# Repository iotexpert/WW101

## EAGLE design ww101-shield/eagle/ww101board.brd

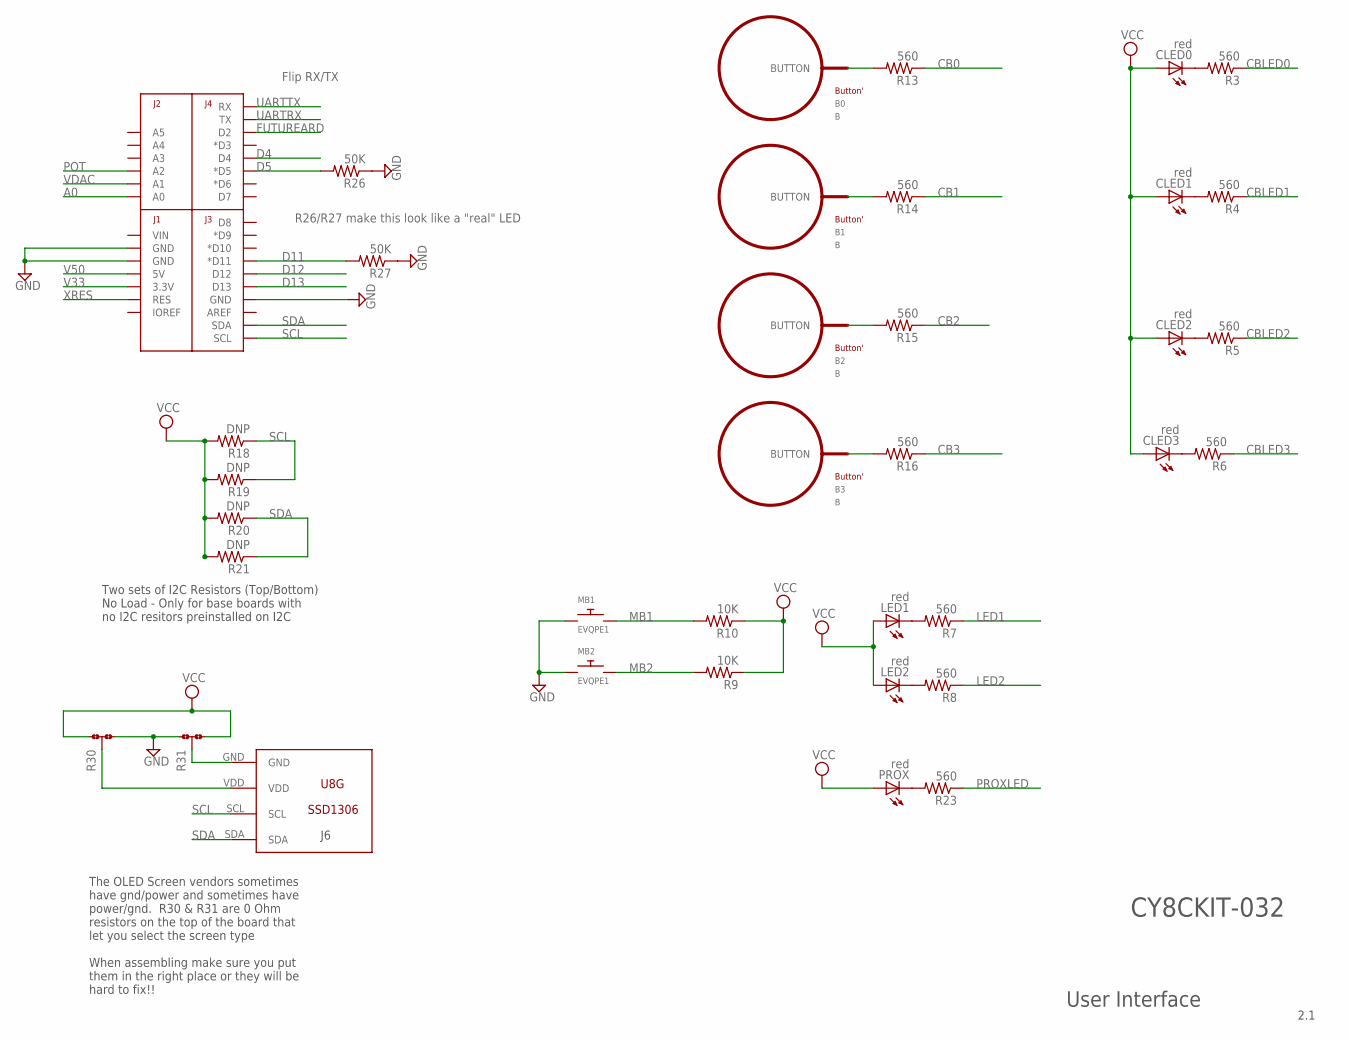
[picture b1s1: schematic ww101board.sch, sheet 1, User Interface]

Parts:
B0, B1, B2, B3: B; BUTTON_PASSIVE_10MM
CLED0, CLED1, CLED2, CLED3: red; CHIP-LED0603
J6: U8G-096-OLED; 096-SSD1306
LED1, LED2: red; CHIP-LED0603
MB1, MB2: EVQPE1; SWITCH
PROX: red; CHIP-LED0603
R3, R4, R5, R6, R7, R8, R13, R14, R15, R16, R23: 560; 0603-RES
R9, R10: 10K; 0603-RES
R18, R19, R20, R21: DNP; 0603-RES
R26, R27: 50K; 0603-RES
R30: JMP-3-1_2
R31: JMP-3-2_3
U$1: ARDUINO_R3_SHIELDNOLABELS; UNO_R3_SHIELD_NOLABELS

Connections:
A0: U$1.A0; also elsewhere on the board
CB0: R13.1; also elsewhere on the board
CB1: R14.1; also elsewhere on the board
CB2: R15.1; also elsewhere on the board
CB3: R16.1; also elsewhere on the board
CBLED0: R3.1; also elsewhere on the board
CBLED1: R4.1; also elsewhere on the board
CBLED2: R5.1; also elsewhere on the board
CBLED3: R6.1; also elsewhere on the board
D4: U$1.D4; also elsewhere on the board
D5: R26.2, U$1.D5 (*D5); also elsewhere on the board
D11: R27.2, U$1.D11 (*D11); also elsewhere on the board
D12: U$1.D12; also elsewhere on the board
D13: U$1.D13; also elsewhere on the board
FUTUREARD: U$1.D2; also elsewhere on the board
GND: MB1.P$1, MB2.P$1, R26.1, R27.1, R30.3, R31.1, U$1.GND@0 (GND), U$1.GND@1 (GND), U$1.GND@2 (GND); also elsewhere on the board
LED1: R7.1; also elsewhere on the board
LED2: R8.1; also elsewhere on the board
MB1: MB1.P$2, R10.2; also elsewhere on the board
MB2: MB2.P$2, R9.2; also elsewhere on the board
unnamed: B0.BUTTON, R13.2
unnamed: PROX.C, R23.2
unnamed: B1.BUTTON, R14.2
unnamed: B2.BUTTON, R15.2
unnamed: CLED0.C, R3.2
unnamed: CLED1.C, R4.2
unnamed: CLED2.C, R5.2
unnamed: CLED3.C, R6.2
unnamed: LED1.C, R7.2
unnamed: LED2.C, R8.2
unnamed: J6.VDD, R30.2
unnamed: B3.BUTTON, R16.2
unnamed: J6.GND, R31.2
POT: U$1.A2; also elsewhere on the board
PROXLED: R23.1; also elsewhere on the board
SCL: J6.SCL, R18.1, R19.1, U$1.SCL; also elsewhere on the board
SDA: J6.SDA, R20.1, R21.1, U$1.SDA; also elsewhere on the board
UARTRX: U$1.TX; also elsewhere on the board
UARTTX: U$1.RX; also elsewhere on the board
V33: U$1.3.3V; also elsewhere on the board
V50: U$1.5V; also elsewhere on the board
VCC: CLED0.A, CLED1.A, CLED2.A, CLED3.A, LED1.A, LED2.A, PROX.A, R9.1, R10.1, R18.2, R19.2, R20.2, R21.2, R30.1, R31.3; also elsewhere on the board
VDAC: U$1.A1; also elsewhere on the board
XRES: U$1.RES; also elsewhere on the board

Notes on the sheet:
Flip RX/TX
User Interface
Two sets of I2C Resistors (Top/Bottom) No Load - Only for base boards with no I2C resitors preinstalled on I2C
The OLED Screen vendors sometimes have gnd/power and sometimes have power/gnd. R30 & R31 are 0 Ohm resistors on the top of the board that let you select the screen type When assembling make sure you put them in the right place or they will be hard to fix!!
2.1
CY8CKIT-032
R26/R27 make this look like a "real" LED

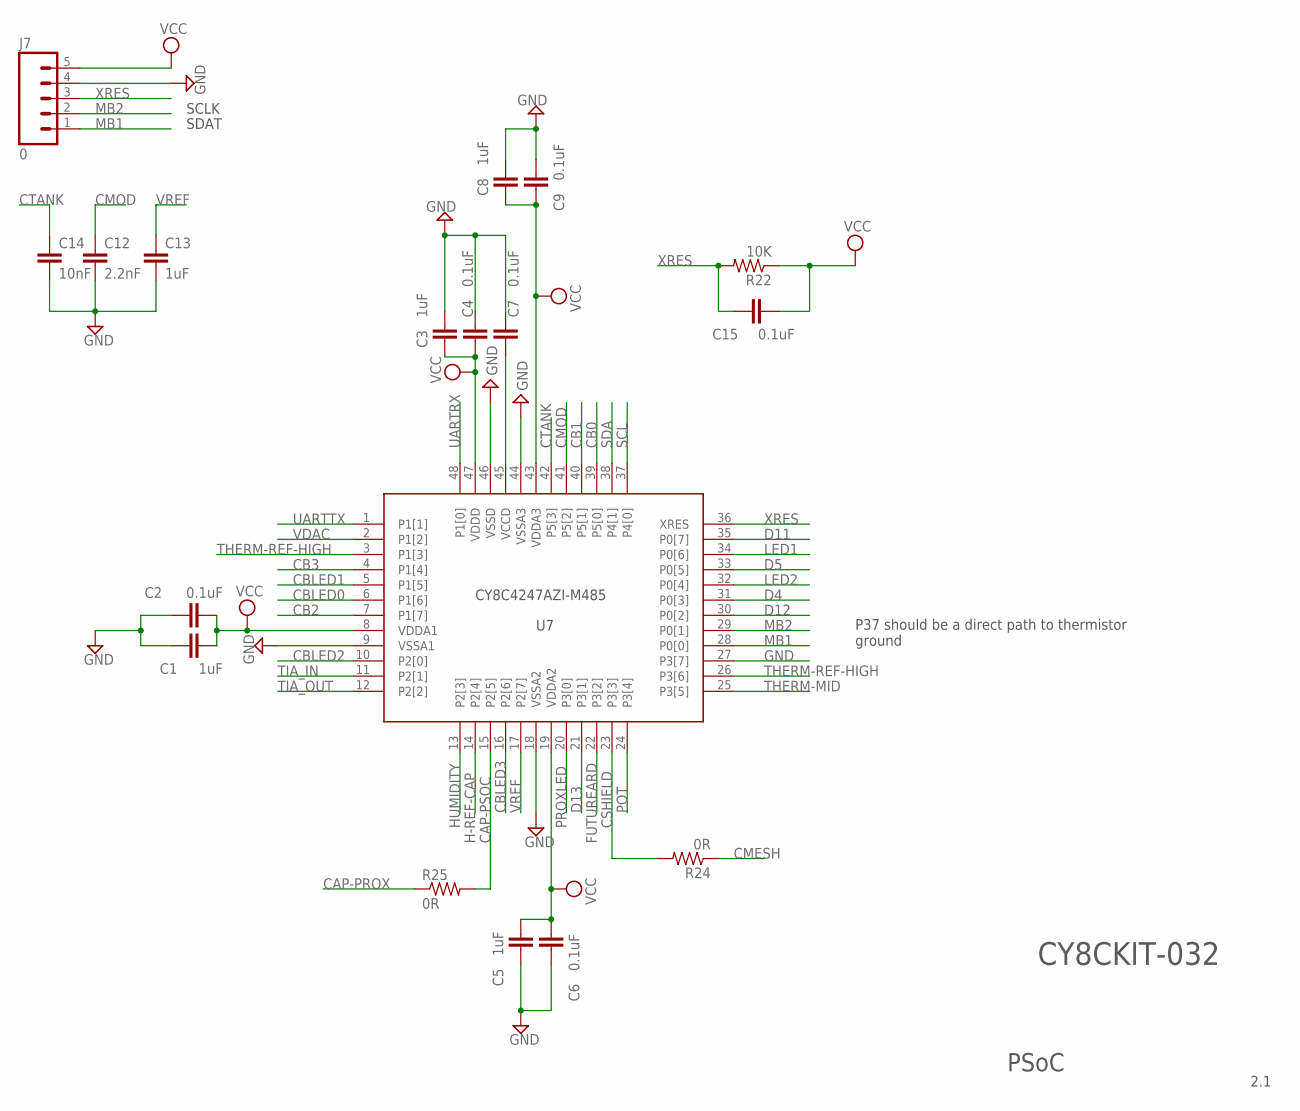
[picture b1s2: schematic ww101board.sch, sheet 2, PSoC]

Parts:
C1, C3, C5, C8, C13: 1uF; 0603-CAP
C2, C4, C6, C7, C9, C15: 0.1uF; 0603-CAP
C12: 2.2nF; 0603-CAP
C14: 10nF; 0603-CAP
J7: 0; 1X05_LOCK
R22: 10K; 0603-RES
R24, R25: 0R; 0603-RES
U7: CY8C4A45-48; TQFP-7X7-48
U$7: CYLOGO-SILK

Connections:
CAP-PROX: R25.1
CAP-PSOC: R25.2, U7.15 (P2[5])
CB0: U7.39 (P5[0]); also elsewhere on the board
CB1: U7.40 (P5[1]); also elsewhere on the board
CB2: U7.7 (P1[7]); also elsewhere on the board
CB3: U7.4 (P1[4]); also elsewhere on the board
CBLED0: U7.6 (P1[6]); also elsewhere on the board
CBLED1: U7.5 (P1[5]); also elsewhere on the board
CBLED2: U7.10 (P2[0]); also elsewhere on the board
CBLED3: U7.16 (P2[6]); also elsewhere on the board
CMESH: R24.1
CMOD: C12.1, U7.41 (P5[2])
CSHIELD: R24.2, U7.23 (P3[3])
CTANK: C14.1, U7.42 (P5[3])
D4: U7.31 (P0[3]); also elsewhere on the board
D5: U7.33 (P0[5]); also elsewhere on the board
D11: U7.35 (P0[7]); also elsewhere on the board
D12: U7.30 (P0[2]); also elsewhere on the board
D13: U7.21 (P3[1]); also elsewhere on the board
FUTUREARD: U7.22 (P3[2]); also elsewhere on the board
GND: C1.1, C2.1, C3.1, C4.1, C5.2, C6.2, C7.1, C8.1, C9.1, C12.2, C13.2, C14.2, J7.4, U7.9 (VSSA1), U7.18 (VSSA2), U7.27 (P3[7]), U7.44 (VSSA3), U7.46 (VSSD); also elsewhere on the board
H-REF-CAP: U7.14 (P2[4]); also elsewhere on the board
HUMIDITY: U7.13 (P2[3]); also elsewhere on the board
LED1: U7.34 (P0[6]); also elsewhere on the board
LED2: U7.32 (P0[4]); also elsewhere on the board
MB1: J7.1, U7.28 (P0[0]); also elsewhere on the board
MB2: J7.2, U7.29 (P0[1]); also elsewhere on the board
unnamed: C7.2, U7.45 (VCCD)
POT: U7.24 (P3[4]); also elsewhere on the board
PROXLED: U7.20 (P3[0]); also elsewhere on the board
SCL: U7.37 (P4[0]); also elsewhere on the board
SDA: U7.38 (P4[1]); also elsewhere on the board
THERM-MID: U7.25 (P3[5]); also elsewhere on the board
THERM-REF-HIGH: U7.3 (P1[3]), U7.26 (P3[6]); also elsewhere on the board
TIA_IN: U7.11 (P2[1]); also elsewhere on the board
TIA_OUT: U7.12 (P2[2]); also elsewhere on the board
UARTRX: U7.48 (P1[0]); also elsewhere on the board
UARTTX: U7.1 (P1[1]); also elsewhere on the board
VCC: C1.2, C2.2, C3.2, C4.2, C5.1, C6.1, C8.2, C9.2, C15.1, J7.5, R22.1, U7.8 (VDDA1), U7.19 (VDDA2), U7.43 (VDDA3), U7.47 (VDDD); also elsewhere on the board
VDAC: U7.2 (P1[2]); also elsewhere on the board
VREF: C13.1, U7.17 (P2[7])
XRES: C15.2, J7.3, R22.2, U7.36 (XRES); also elsewhere on the board

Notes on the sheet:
SCLK
SDAT
PSoC
2.1
CY8C4247AZI-M485
CY8CKIT-032
P37 should be a direct path to thermistor ground

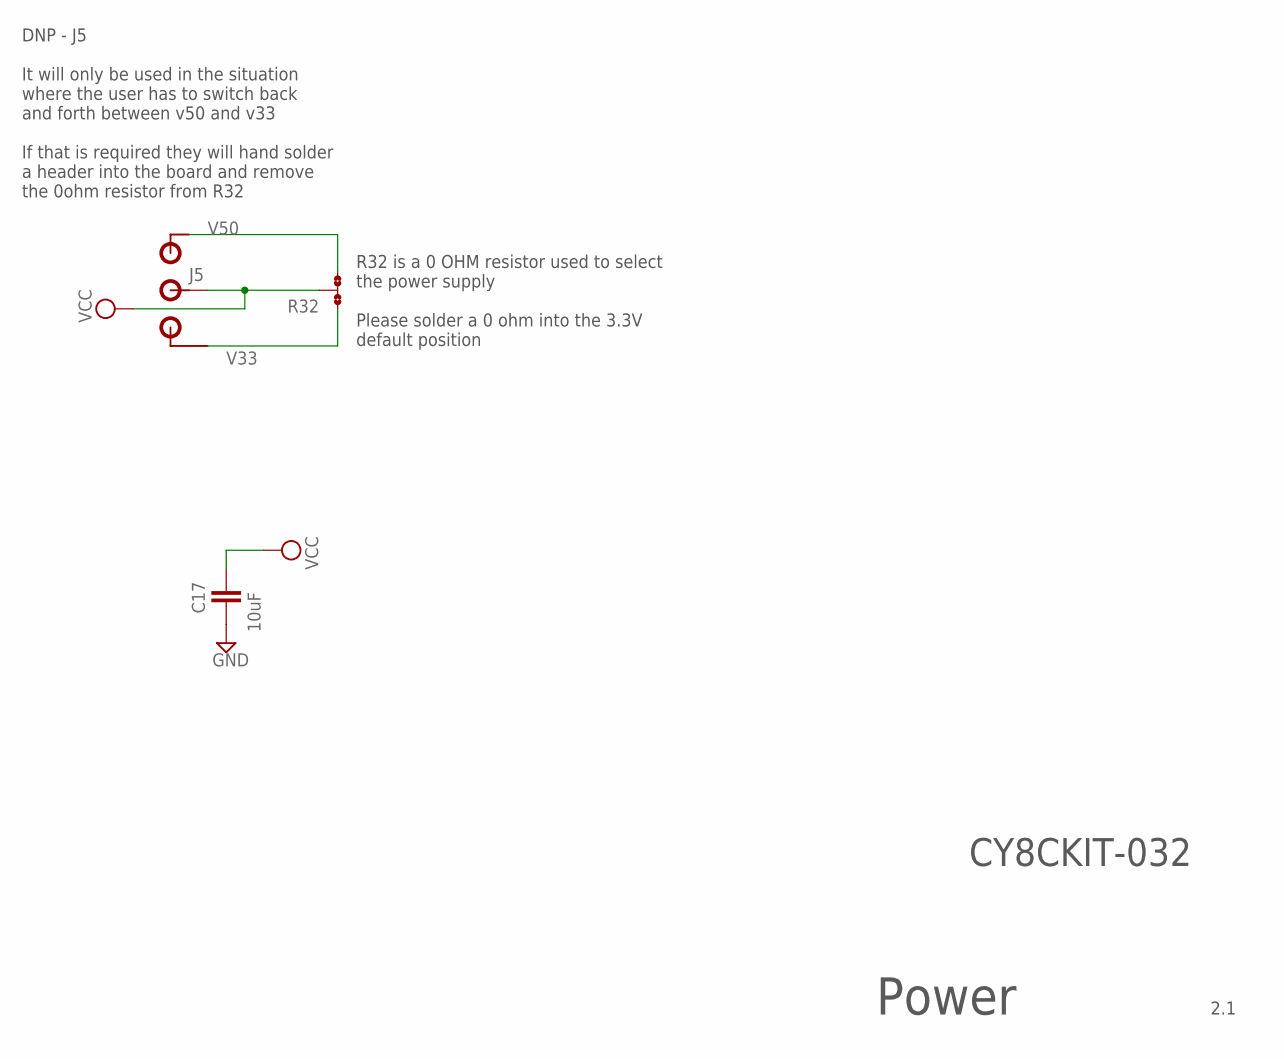
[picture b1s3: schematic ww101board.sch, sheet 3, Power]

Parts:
C17: 10uF; 0603-CAP
J5: JMP-3-PTH-PTH; JMP-3-NO-PTH-2.54
R32: JMP-3-NO

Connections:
GND: C17.2; also elsewhere on the board
V33: J5.3, R32.1; also elsewhere on the board
V50: J5.1, R32.3; also elsewhere on the board
VCC: C17.1, J5.2, R32.2; also elsewhere on the board

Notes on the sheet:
Power
2.1
DNP - J5 It will only be used in the situation where the user has to switch back and forth between v50 and v33 If that is required they will hand solder a header into the board and remove the 0ohm resistor from R32
R32 is a 0 OHM resistor used to select the power supply Please solder a 0 ohm into the 3.3V default position
CY8CKIT-032

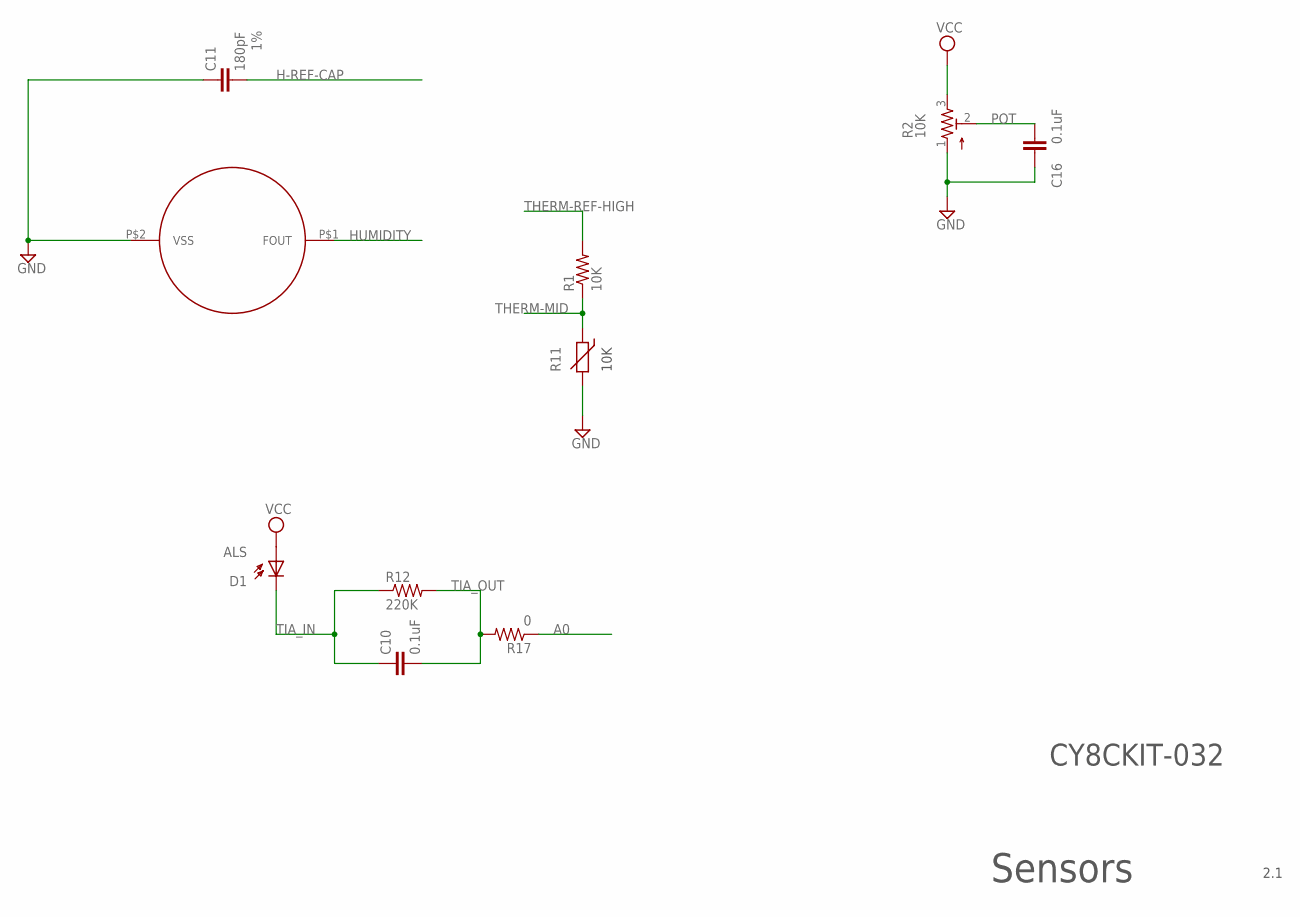
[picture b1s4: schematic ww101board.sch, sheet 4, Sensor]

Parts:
C10, C16: 0.1uF; 0603-CAP
C11: 180pF; 0603-CAP
D1: ALS
HUMIDITY: HPP801A031; HUMIDITY
R1: 10K; 0603-RES
R2: 10K; 3386P
R11: THERMISTOR-5; R-5
R12: 220K; 0603-RES
R17: 0; 0603-RES

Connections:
A0: R17.1; also elsewhere on the board
GND: C11.1, C16.2, HUMIDITY.P$2 (VSS), R2.1, R11.2; also elsewhere on the board
H-REF-CAP: C11.2; also elsewhere on the board
HUMIDITY: HUMIDITY.P$1 (FOUT); also elsewhere on the board
POT: C16.1, R2.2; also elsewhere on the board
THERM-MID: R1.1, R11.1; also elsewhere on the board
THERM-REF-HIGH: R1.2; also elsewhere on the board
TIA_IN: C10.1, D1.CATHODE (C1), R12.1; also elsewhere on the board
TIA_OUT: C10.2, R12.2, R17.2; also elsewhere on the board
VCC: D1.ANNODE (E1), R2.3; also elsewhere on the board

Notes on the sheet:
Sensors
10K
2.1
CY8CKIT-032

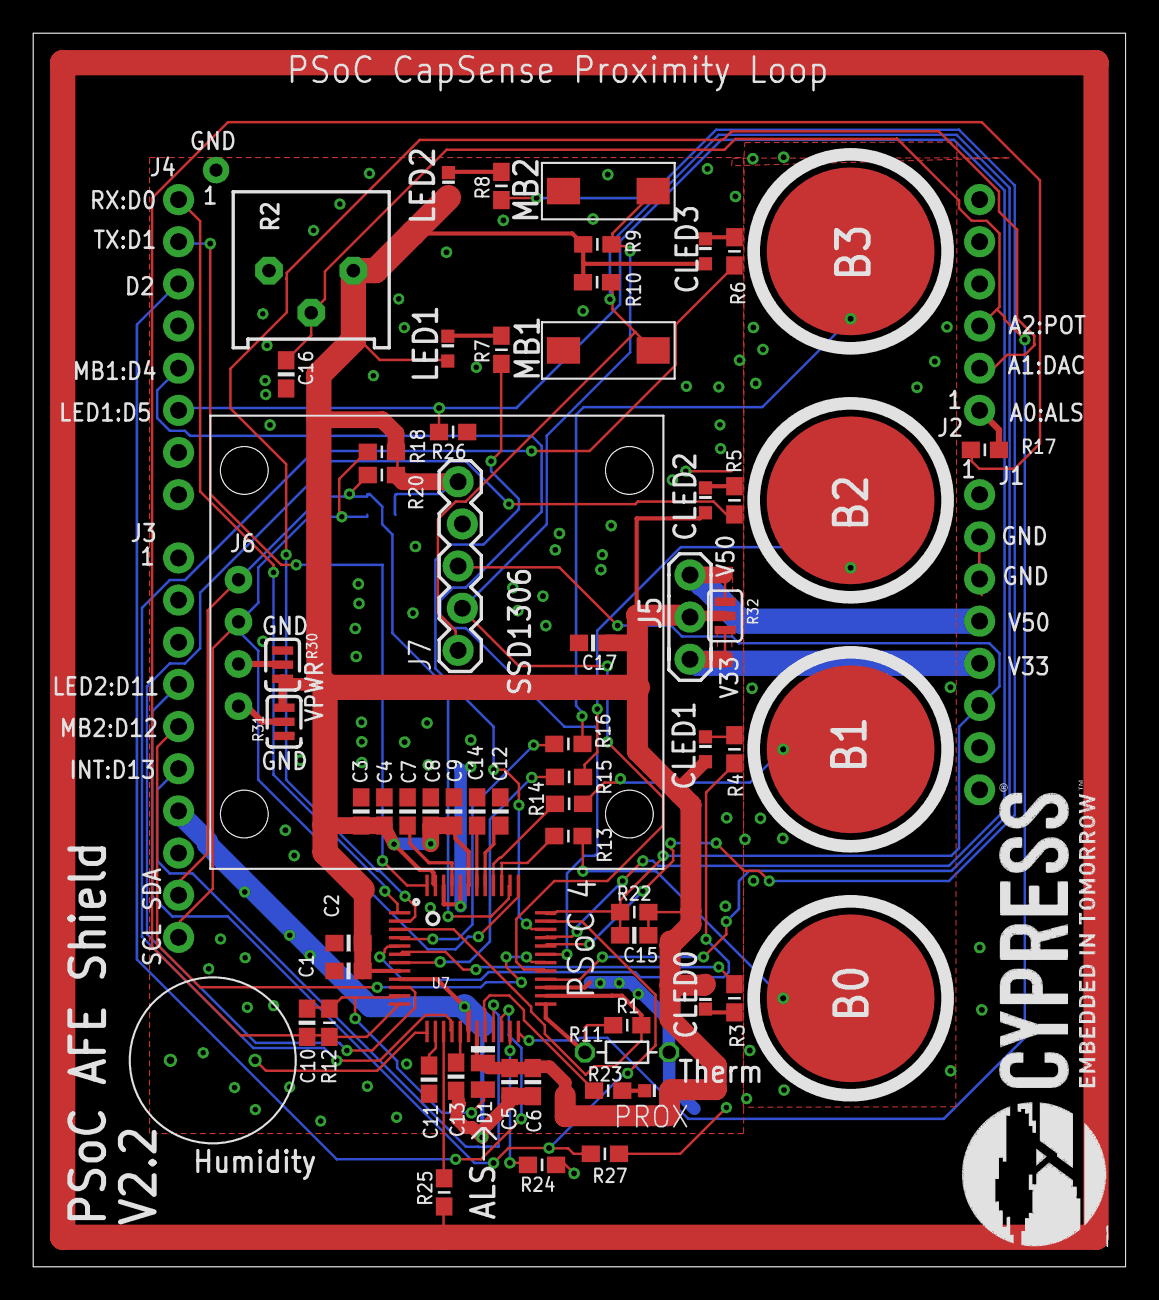
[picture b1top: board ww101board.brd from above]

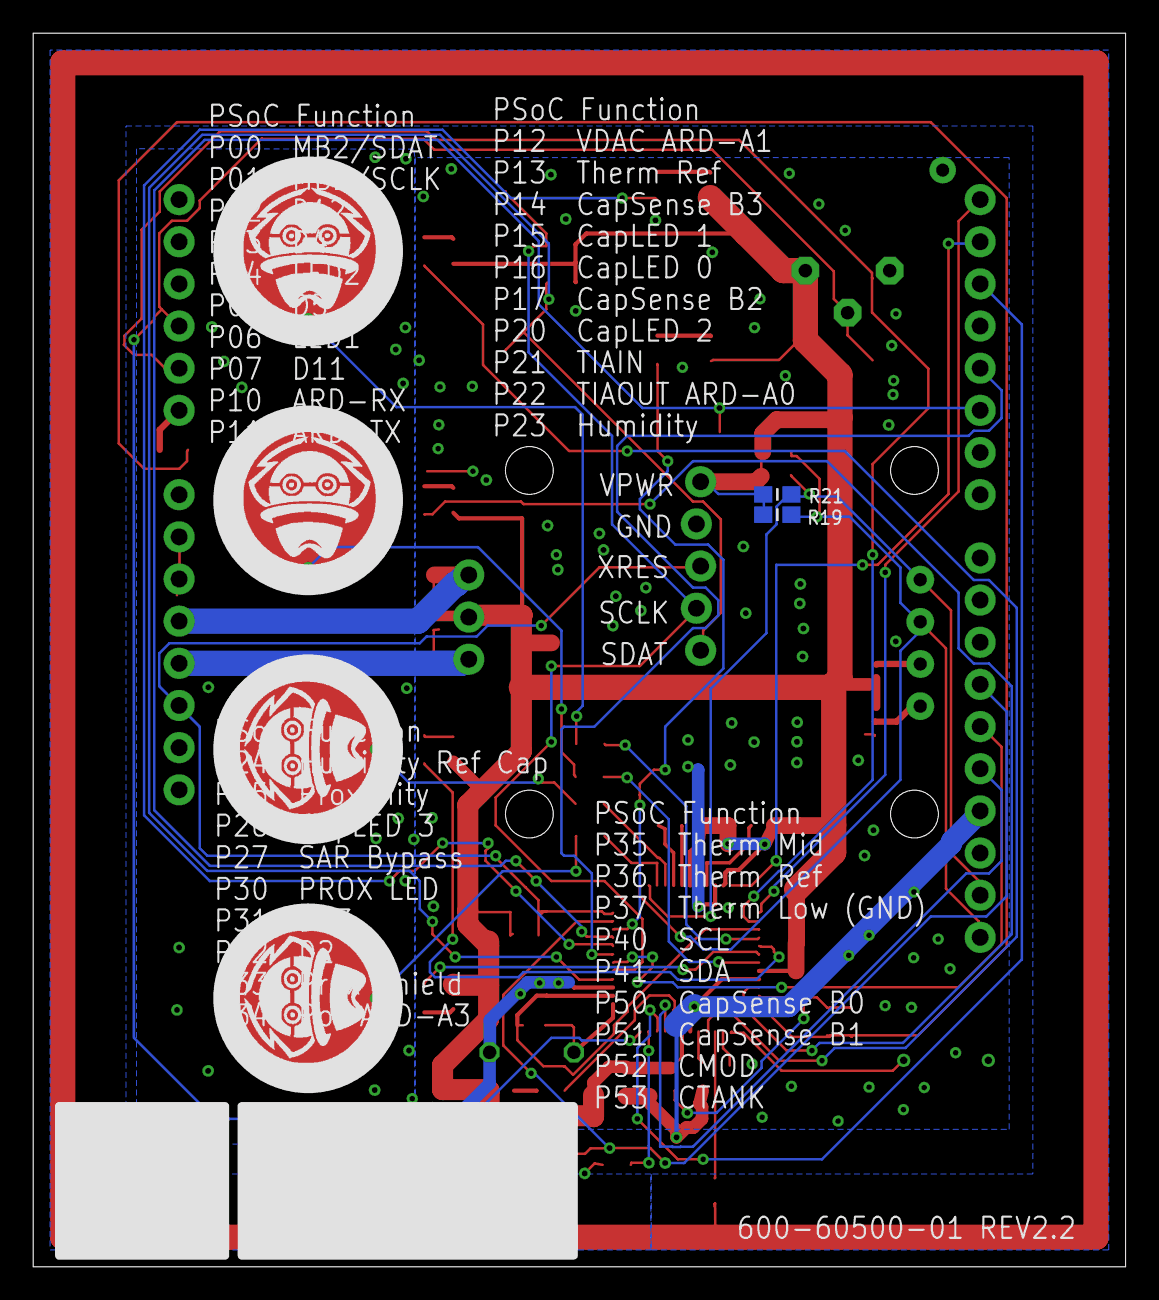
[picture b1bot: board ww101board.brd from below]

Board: 2 copper layers, 65.8 x 74.3 mm, 68 parts (2 on the bottom side), 56 nets.

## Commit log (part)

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2016-10-11 moved old single page lab manual
2016-10-12 Add material and exercises up through 10.
2016-10-12 Fix reference about USB connector on analog shield board.
2016-10-12 Move the WICED projects down one level.
2016-10-13 Bunches of updates to chapter 3,6,9
2016-10-13 Add BCM9493W Platform Files
2016-10-13 Add page numbers. Fix typos/wording. Fix figure for MUTEX documentation to be consistent with others.
2016-10-13 Add page numbers and make minor corrections.
2016-10-14 Remove .Greg file.
2016-10-15 Add codegentemp and .Greg to .gitignore. Update chapter 8. Fix PSoC project to have open drain, drives low on LED pins and to add external components to LEDs.
2016-10-17 Minor updates and type corrections.
2016-10-17 Checkin of labs for chapter 3 (RTOS).
2016-10-19 a little bit of reorganization
2016-10-19 project-list.xlsx
2016-10-19 Add example projects and errata sections. Fix typo in mutex project.
2016-10-20 first real draft of chapter 5
2016-10-20 updated based on JAMD comments
2016-10-21 Correct typos in chapters 00, 01, and 05
2016-10-21 a few updates to chapter 6'
2016-10-21 A bunch of updates
2016-10-22 Updates chapter 6a based on GJL and JAMD feedback
2016-10-22 massive updates to 5,6,7
2016-10-25 Formatting updates
2016-10-25 updated chapter 4
2016-10-25 Fix typos
2016-10-26 New answer key file and updates to 7a/7b.
2016-10-26 coverpage
2016-10-26 Initial checkin of chap 7b projects
2016-10-30 Updates after pilot class. Add pull down to LED pin on shield board
2016-10-31 Typo correction
2016-11-03 corrections in chapter 6 & make app name strings unique in project make files. git push origin gjl_oct23
    git status
2016-11-20 Updated the project and section for DCT in chapter 5
2016-11-20 Updates chapter 5 projects
2016-11-30 Updates to the server
2016-11-30 More updates to the TCP section
2016-12-02 fixed bug
2016-12-05 Updates prior to WW50 class. All projects and manuals modified for Wiced Studio 4.0 and other changes from pilot class.
2016-12-05 Rename labmanual files from WA101 to WW101 (WICED WiFi 101).
2016-12-05 Change project name from WA101 to WW101_AnalogCoprocessor
2017-01-24 smalls edits in chapters 2, 3, 5, 6. Full cleanup for chapters 0, 1
2017-01-31 Change TCP socket exampls to be stream first and packet second.
2017-01-31 add latest 048 files
2017-02-01 added a version number textbox to the cover
2017-02-01 fix server so that it can get peer IP even if peer disconnects first
2017-02-01 More cleanup and rewording. Fixed some formatting. Addressed master book comments in chapters 3,4,5
2017-02-02 fix uartsend/receive projects for 9600 baud. Update document regarding uart, add additional details regarding the timer function to the RTOS chapter
2017-02-02 Added the streams section in the lecture materials, changed exercise 02 to streams, changed exercise 03 to packets
2017-02-02 Made manual updates to the chapter 07 material
2017-02-03 minor updates and add response isnsructions to exercise 3
2017-02-03 fix typo
2017-02-03 update all of the instructions and sceen captures for AWS web changes
2017-02-03 remove old certificates and keys
2017-02-04 add instruction to activate certificate. remove home WiFi router info from dct.h
2017-02-06 fix instructions to use * for poplicy ARN and to tell user to run clean after updating certificate/key
2017-02-07 fix description of client.cer in lab exercise
2017-02-07 fix explanation of lab 5 regarding separate certificates
2017-02-08 first files for shield
2017-02-09 added description file
2017-02-10 first complete route of board
2017-02-10 routing complete
2017-02-10 added BOM
2017-02-11 Updated BOM
2017-02-11 Fixed resistors
2017-02-15 Right before diode move
2017-02-15 0.99 version of PCB
2017-02-15 A few more changes to the silkscreen
2017-02-26 Fully implemented (but not fully debugged) shield firmware
2017-02-27 fix DAC issue, fix humidity issue. Remaining issues are proximity and smartio
2017-02-27 fix smartIO issue
2017-03-01 Major update to the test program
2017-03-01 New exercises for chapter 4 (u8g graphics).
2017-03-02 Fixed bugs in base shield firmware
2017-03-02 uodated example projects for the BCM943907AEVAL1_WW101
2017-03-02 add new platform files for BCM943907AEVAL1F_WW101
2017-03-02 fix names of LED0 and LED1 pins. Change bootloader to Release build.
2017-03-02 Add instrucions on putting 044 kit into bypass mode.
2017-03-03 Update CapSense tuning. Add LEDs to the CapSense tuning project including LED1 for Proximity.
2017-03-04 added Azure tools bins for simulating a device, reading a device, and creating a client id. Also updated the 07_pwm solution
2017-03-04 Fix typo on OLED control in Appendix B.
2017-03-06 Update for new shield.
2017-03-06 Add 2nd set of valid credentials for the subscriber/publisher combo exercise.
2017-03-08 Move manuals to English subfolder
2017-03-08 Checkin Chinese manual used in Shanghai.
2017-03-08 Move supplemental file to sub dir and remove original outline
2017-03-09 Change back order of project, shield and glossary sections
2017-03-10 Remove info about the PSoC driving the OLED since it is not yet implemented.
2017-03-10 adding azure tools
2017-03-14 Remove versions of projects that were renumbered.
2017-03-17 Checkin pdf files of the manual, updates to all manual sections.
2017-03-17 Remove COrtexM0 files from test program project.
2017-03-20 Initial checkin
2017-03-23 Add RKAD board changes.
2017-04-04 Updates to manual from Europe feedback and for the CYW943907AEVAL1F kit.
2017-04-06 Fix typo in debug command.
2017-04-11 Update manual to remove while(1) from main if other threads are doing all the work.
2017-04-11 Un-checkin the AVN manual copy.
2017-05-16 Remove open and WEP network.
2017-05-30 Add CYW... kit platform files
2017-05-30 Update password for new router.
2017-06-05 Update schematic of the base board to a searchable version.
2017-06-05 Updates after SJ class in WW1722. Chapter 2 and 4: I2C: use separate read/write instead of transfer Chapter 5: Change LED blinking to be easier to remember. Chapter 6: Change server from Ethernet to 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
2017-06-06 Add REST definition to glossary Add driver installation instructions
2017-06-06 Change name of shield to match the latest hardware.
2017-06-07 Update pdf for survey
2017-06-07 Minor updates to broker machine description
2017-06-09 draft of 6
2017-06-09 Reformat
2017-06-09 formatting and minor re-wording
2017-06-12 A bunch of updates on Chapter 6
2017-06-12 Minor corrections and rewording
2017-06-14 minor changes to the certificates section
2017-06-14 Fix wording on certificate section and drawing.
2017-06-16 a major re-org of chap6 ... and a total re-write of the server
2017-06-17 Finished server
2017-06-18 05 secure server
2017-06-18 Started WW06 changes
2017-06-19 Update partner slide with Michael Fortner's slides. Update project to have new location for certificate files.
2017-06-21 Complete class project and update instructions.
2017-06-22 Update CapSense buttons to manual tuning but Humidity to auto-tune.
2017-06-29 updates to name of files
2017-06-29 some updates to the outline... plus chatper 3 introduction
2017-06-29 New file
2017-06-29 updated chapter 3
2017-06-29 New files for videos
2017-06-29 Revert
2017-06-30 a few updates for my voice
2017-06-30 Updates for uart voice
2017-06-30 minor updates to chapter 1
2017-07-13 updated mutex video script
2017-07-13 Fix warning.
2017-07-13 Regenerate PDFs of lab manuals (causes modification to docx time stamp too)
2017-07-17 changed make file for 05_secure_server
2017-07-17 Change unsecure and insecure to non-secure. Minor formatting chagnes. Add exercie 6.
2017-07-17 fixed dual client and dual server
2017-07-18 Updates for TLS
2017-07-18 More updates to the TLS Chapter and projects
2017-07-18 Formatting changes and re-create pdfs.
2017-07-19 Update dual client so that it indicates which type of message is being sent.
2017-07-20 Update version number
2017-07-21 Update I2C to indicate why speed must be set to standard.
2017-07-24 Intermediate updates to labmanual
2017-07-30 changes to the http document
2017-07-30 updates to the speaker notes
2017-07-31 updates to 7a and 7b speaker notes
2017-07-31 Minor updats and formatting
2017-07-31 Fix formatting.
2017-07-31 Rename chapter 7a and 7b
2017-08-29 Updates to material after Ukraine. Change shield LED and button names to match base board.
2017-08-29 Rename 02 to 02b to keep in order.
2017-08-29 Change revision to 1.4
2017-09-05 intermediate update to template
2017-09-06 Checking chap 4 and 5 scripts using new template.
2017-09-07 First update to chapter 3
2017-09-12 Update formatting on all sections
2017-09-13 Minor corrections/updates
2017-09-13 Updates to chapter 7c
2017-09-21 fixed numbering on chap 8 and 9
2017-09-27 Update manual for 07b as AWS, 07c as HTTP, and 07d as MQTT. Also affects the signoff sheet, intro (agenda) and class project. The revision on the binder is now 2.1.
2017-09-27 Add solutions for HTTP chapter exercises 1, 3, 4, and 5.
2017-09-28 Fix instructions to use curl on Windows
2017-10-01 V2.0 of board
2017-10-09 Fixed DRC and moved Resistor
2017-10-09 New MQTT chapter
2017-10-09 Fixed 7d numbering
2017-10-09 Redo firmware and documents for new pinout. Update formatting of all chapters. Add platform files for new shield pinout.
2017-10-09 Update text on screen when waiting for the kit.
2017-10-11 u8g lib moved into firmwaer folder
2017-10-11 updated pdf of schematic
2017-10-11 Remove reference to class certs from the class project. Update project name in the shield section.
2017-10-13 before library update
2017-10-16 a bunch of minor tweaks
2017-10-17 updates to 2.1 board based on GJL inputs
2017-10-17 Swap MB1/MB2 in firmware Refactor main.c to put each system processing in a separate function.
2017-10-19 edits to the videos
2017-10-24 Fix PWM error in chapter 2 solution. Fix initial I2C read issue in weather station. Checkin scripts for videos for chapters 4, 5, 6, and 8. Checking updates to bootloader entry for shield.
2017-10-25 New chapger 2-1B to explain custom platform files.
2017-10-25 Fix typo.
2017-10-26 Added R26/R27 Pulldowns on LED pins from arduino
2017-10-26 Updates for resistor jumpers ... and new gerbers
2017-10-30 Checkin platforom files for shield version 1 checkin firmware updates for V2.2 prior to code review.
2017-10-30 ARH updates to manual
2017-10-30 Add new files for WICED Studio 6.0 makefiles
2017-10-30 Updatre platfrom files
2017-10-31 Add spreaker notes for newly formatted chapter 7 including HTTP
2017-11-02 Hopefully final V2.2 board
2017-11-02 Updae EROS and IROS prior to ES10.
2017-12-06 Update chapter 7 projects for new HTTP chapter.
2017-12-06 Update firmware for V2.2 shield release
2017-12-06 Add platform for the Nebula kit
2017-12-11 Fix paragraph numbering
2017-12-13 Cleaned up FW and removed all unnecessary files. Fixed bugs found by BHAT during OOB review.
2018-01-02 Update tls to check for host name in certificate. Fix typo in app name in make files
2018-01-23 New HTTP chapter, change AWS account name.
2018-01-25 Checkin official kit FW from P4.
2018-01-25 Minor updates to manual.
2018-02-01 Checkin new spakernotes.
2018-02-05 Improve comments regarding active high/low LEDs
2018-02-06 Minor format changes.
2018-03-26 Split up chapter 6 into 6A (sockets) and 6B (TLS)
2018-03-26 Updates to projects. Split chap 6 projects into 6A (Socekts) and 6B (TLS)
2018-03-26 Simplfy JSON projects.
2018-03-28 Update labs to make it clear the CLIENT_ID is the AWS thing name.
2018-04-11 Re-arrange files for CYU class submission.
2018-06-06 Update chap 7c manual for new AWS hierarchy in WICED 6.2. Update class setup instructions.
2018-06-12 Fix file list for chap 7 reorg.
2018-06-25 Fix typo in server name
2018-06-27 UPdate for 6.2 libraries.
2018-07-23 Move files so that Manual folders have only what goes in the book.
2018-08-07 Updated Manual PDF files
2018-08-07 Uploaded Class Instructions Source
2018-08-07 Uploaded Changes document
2018-08-07 Uploaded Binder Cover PDF
2018-08-27 Minor update to instructions for 3-ring binder option.
2018-09-18 Add scripts for chap 7
2018-09-19 Updated 7-4 video script
2018-09-22 Chapter 7 video checkin. Minor changes to chap 7b and 7c.
2018-09-27 Fix incorrect PDF file checkin

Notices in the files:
parts and their libraries:
ww101board: License : http://creativecommons.org/licenses/by-sa/3.1/ (Creative Commons 3.1)
ww101board: License : http://creativecommons.org/licenses/by-sa/4.0
(Creative Commons 4.0)
